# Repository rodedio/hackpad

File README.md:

# hackpad
a hachpad how i like it

# case

# scamatic
a hachpad how i like it

This is my Scapatic for my hackpad. I've changed it three times, but this is what I finally came up with and went with. I'm going for a Matrix-style button layout. The socket will be connected to an OLED screen.

# pcb
This is the circuit board. I still had to make a few minor adjustments to the schematic. I added an extra knob. The rotary encoder adjusts the volume on my computer and displays it through a menu on the OLED screen. Allis included a 3D model so I can make it look better in 3D.

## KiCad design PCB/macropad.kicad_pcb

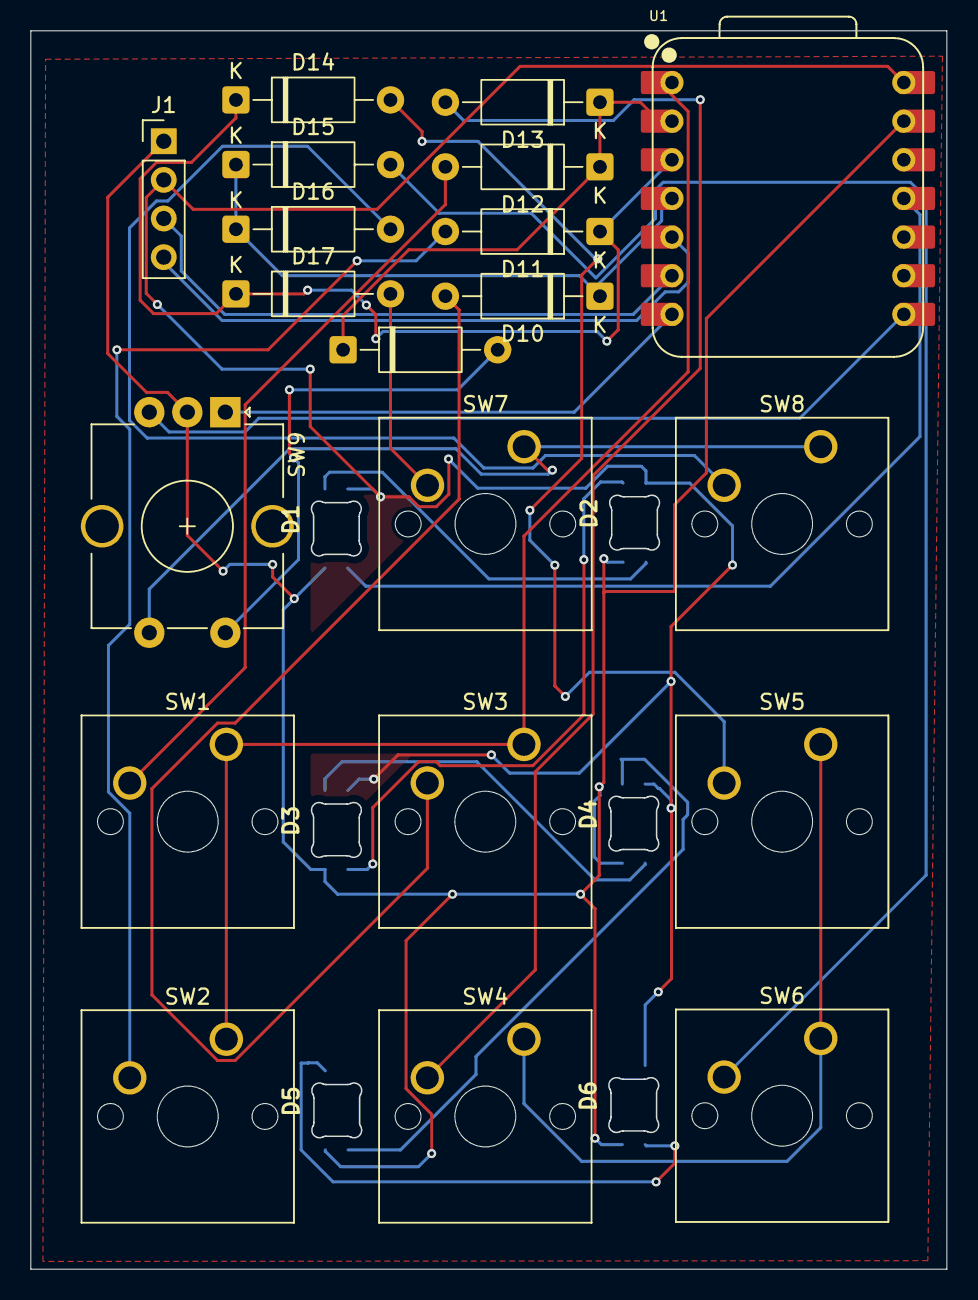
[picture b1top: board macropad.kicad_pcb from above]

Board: 2 copper layers, 60.2 x 81.4 mm, 26 parts (0 on the bottom side), 27 nets.

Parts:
D1, D2, D3, D4, D5, D6: SK6812; SK6812MINI-E_fixed
D10, D11, D12, D13, D14, D15, D16, D17, D18: 1N4148WT; D_A-405_P10.16mm_Horizontal
J1: Conn_01x04_Socket; PinHeader_1x04_P2.54mm_Vertical
SW1, SW2, SW3, SW4, SW5, SW6, SW7, SW8: SW_Push; SW_Cherry_MX_1.00u_PCB
SW9: RotaryEncoder_Switch_MP; RotaryEncoder_Alps_EC12E-Switch_Vertical_H20mm_CircularMoun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
U1: XIAO-RP2040-DIP

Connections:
+5V: D1.3 (VDD), D2.3 (VDD), D3.3 (VDD), D4.3 (VDD), D5.3 (VDD), D6.3 (VDD), J1.2, U1.14 (VBUS)
GND: D1.1 (VSS), D2.1 (VSS), D3.1 (VSS), D4.1 (VSS), D5.1 (VSS), D6.1 (VSS), J1.1, SW9.C, U1.13 (GND)
unnamed: D1.4 (DOUT), D2.2 (DIN)
unnamed: D2.4 (DOUT), D3.2 (DIN)
unnamed: D3.4 (DOUT), D4.2 (DIN)
unnamed: D4.4 (DOUT), D5.2 (DIN)
unnamed: D5.4 (DOUT), D6.2 (DIN)
unnamed: D10.2 (A), SW3.2
unnamed: D11.2 (A), SW2.2
unnamed: D12.2 (A), SW1.2
unnamed: D13.2 (A), SW4.2
unnamed: D14.2 (A), SW5.2
unnamed: D15.2 (A), SW6.2
unnamed: D16.2 (A), SW8.2
unnamed: D17.2 (A), SW7.2
unnamed: D18.2 (A), SW9.S1
unnamed: SW4.1, SW5.1, SW6.1
unnamed: SW7.1, SW8.1, SW9.S2
unnamed: SW9.A, U1.7 (GPIO0/TX)
unnamed: SW9.B, U1.8 (GPIO1/RX)
col0: SW1.1, SW2.1, SW3.1, U1.1 (GPIO26/ADC0/A0)
led: D1.2 (DIN), U1.11 (GPIO3/MOSI)
row0: D12.1 (K), D13.1 (K), D18.1 (K), U1.2 (GPIO27/ADC1/A1)
row1: D11.1 (K), D14.1 (K), D17.1 (K), U1.3 (GPIO28/ADC2/A2)
row2: D10.1 (K), D15.1 (K), D16.1 (K), U1.4 (GPIO29/ADC3/A3)
scl: J1.3, U1.6 (GPIO7/SCL)
sda: J1.4, U1.5 (GPIO6/SDA)

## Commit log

2026-01-15 Enhance README with hackpad details and image
    Added a description and image for the hackpad.
2026-01-17 Expand README with scamatic and pcb details
    Added sections for 'scamatic' and 'pcb' with images.
2026-02-06 Add image to README for case illustration
2026-03-04 Add 'case' section to README
    Added a new section for 'case' in the README.
2026-03-04 Fix header case and add images to README
    Corrected header formatting and added images.
2026-03-04 Rename .gitkeep to hallo
2026-03-04 Rename hackpad.f3d to hackpad case.f3d
2026-03-11 Update bestand.txt with personal notes
2026-03-16 Update README to remove images and case section
    Removed several images and the case section from the README.
2026-03-16 Add initial pcb file
2026-03-18 Replace and add images in README.md
    Updated the image in the README and added a new image.
2026-03-22 Update README with additional images in case section
    Added two new images to the case section of the README.
2026-03-22 Update images in README.md case section
    Removed two images and added two new images in the case section of the README.
